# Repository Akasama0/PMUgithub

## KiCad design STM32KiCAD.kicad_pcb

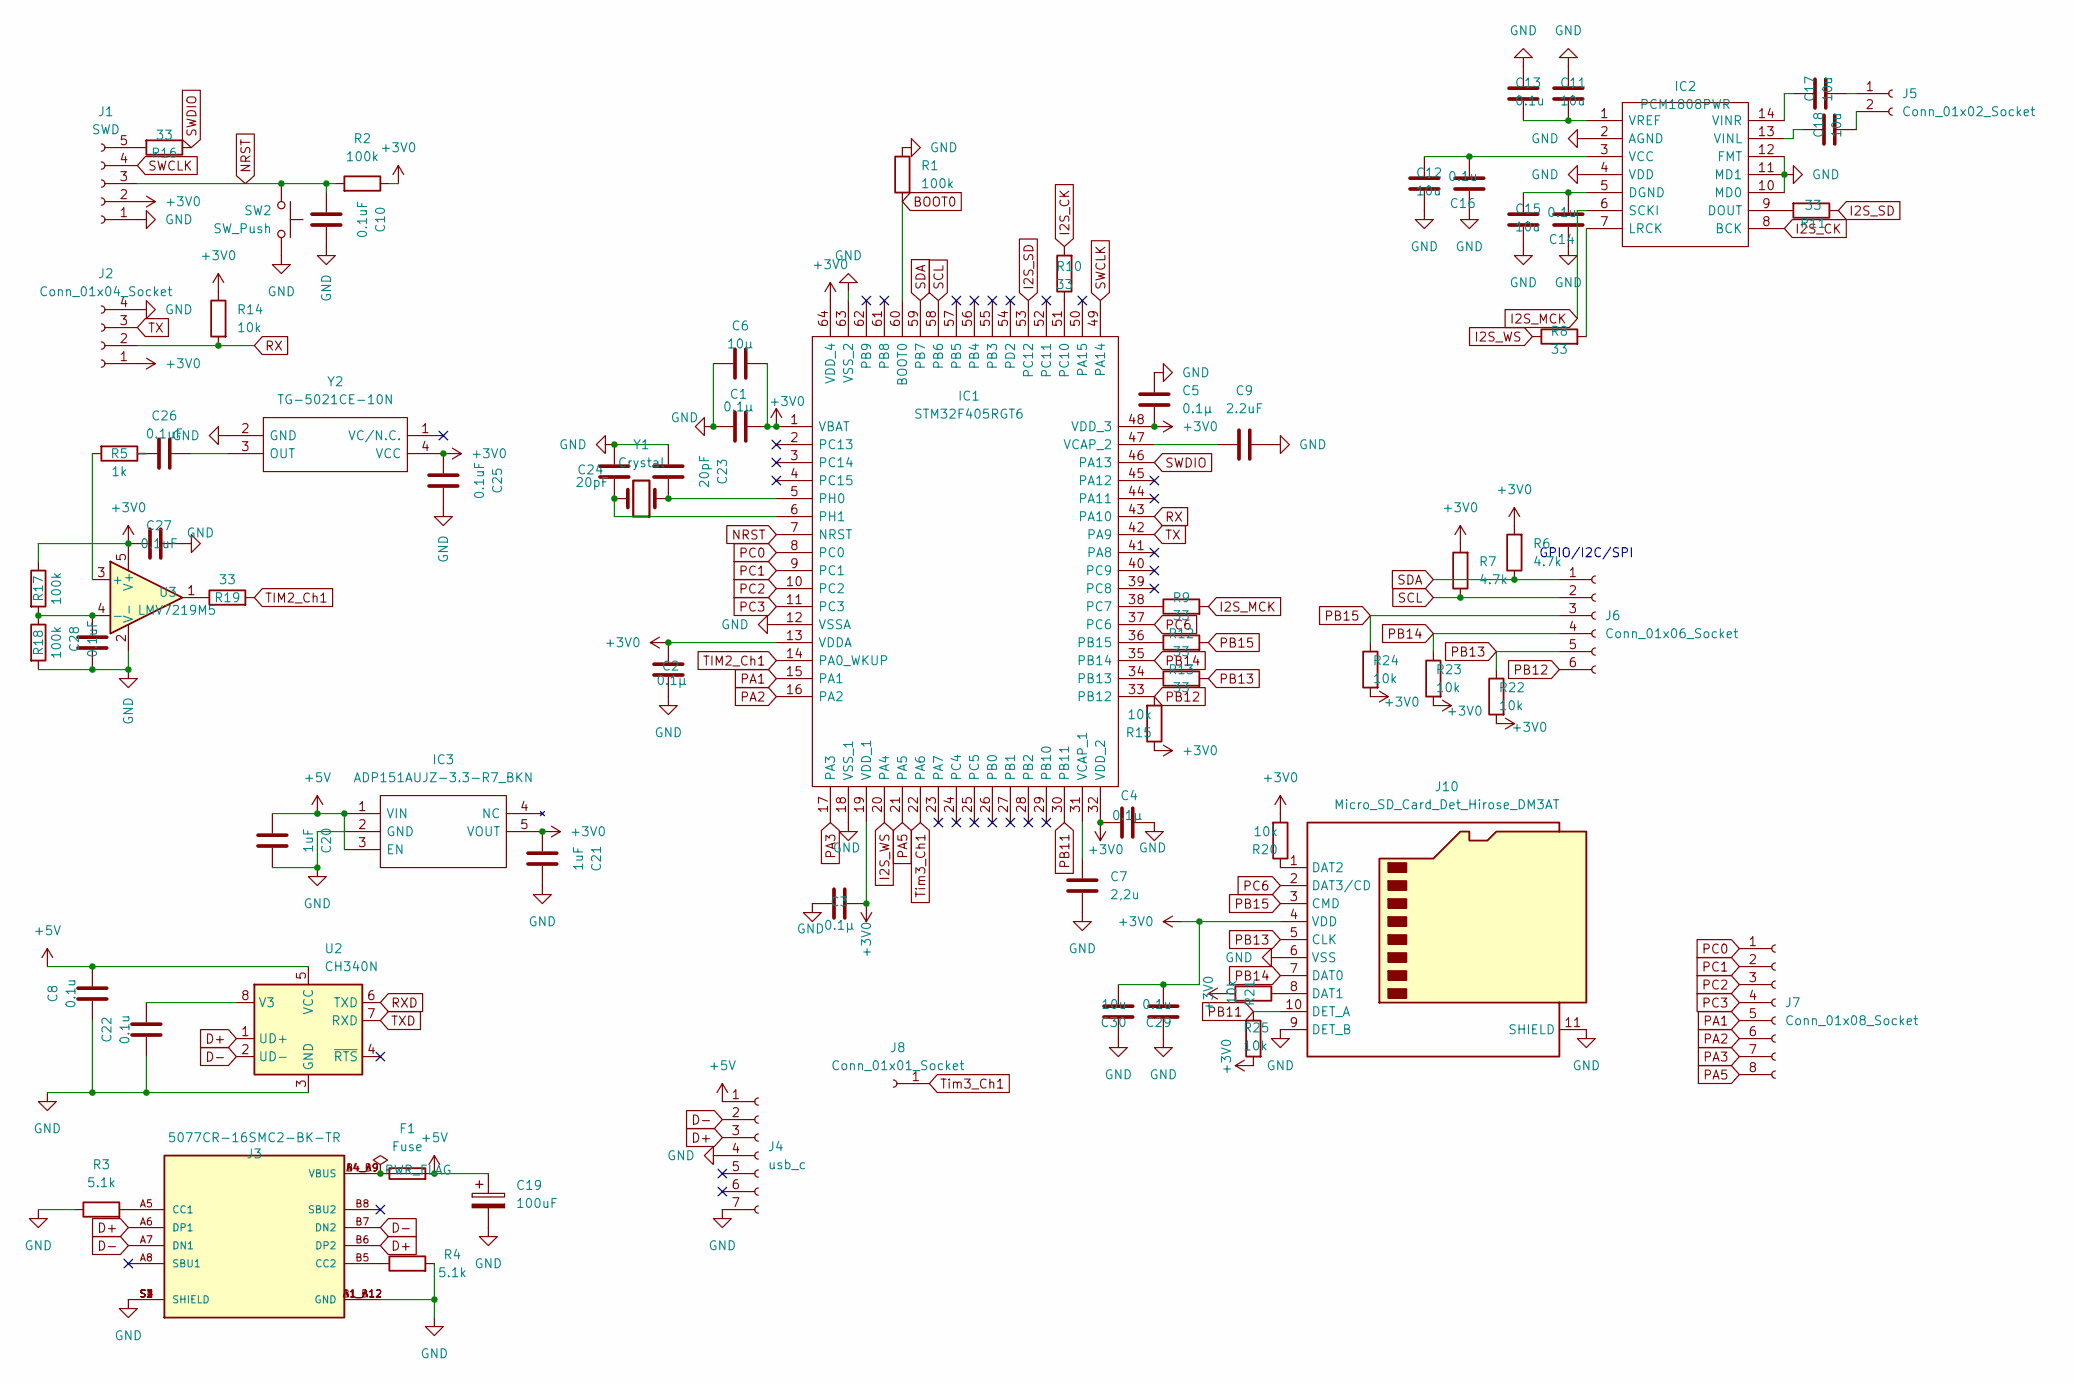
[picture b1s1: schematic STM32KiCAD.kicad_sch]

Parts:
C1, C2, C3, C4, C5: 0.1μ; C_0603_1608Metric_Pad1.08x0.95mm_HandSolder
C6: 10μ; C_0603_1608Metric_Pad1.08x0.95mm_HandSolder
C7: 2,2u; C_0603_1608Metric_Pad1.08x0.95mm_HandSolder
C8, C13, C14, C16, C22, C29: 0.1u; C_0603_1608Metric_Pad1.08x0.95mm_HandSolder
C9: 2.2uF; C_0603_1608Metric_Pad1.08x0.95mm_HandSolder
C10, C25, C26, C27, C28: 0.1uF; C_0603_1608Metric_Pad1.08x0.95mm_HandSolder
C11, C12, C15, C17, C18, C30: 10u; C_0603_1608Metric_Pad1.08x0.95mm_HandSolder
C19: 100uF; C_Radial_D5.0mm_H5.0mm_P2.00mm
C20, C21: 1uF; C_0603_1608Metric_Pad1.08x0.95mm_HandSolder
C23, C24: 20pF; C_0603_1608Metric_Pad1.08x0.95mm_HandSolder
F1: Fuse; Fuse_BelFuse_0ZRE0055FF_L14.0mm_W4.1mm
IC1: STM32F405RGT6; QFP50P1200X1200X160-64N; Manufacturer_Part_Number STM32F405RGT6; Mouser Part Number 511-STM32F405RGT6
IC2: PCM1808PWR; Manufacturer_Part_Number PCM1808PWR; Mouser Part Number 595-PCM1808PWR
IC3: ADP151AUJZ-3.3-R7_BKN; SOT95P280X100-5N; Manufacturer_Part_Number ADP151AUJZ-3.3-R7/BKN
J1: SWD; PinSocket_1x05_P2.54mm_Vertical
J2: Conn_01x04_Socket; PinSocket_1x04_P2.54mm_Vertical
J3: 5077CR-16SMC2-BK-TR; NELTRON_5077CR-16SMC2-BK-TR; PARTREV B
J4: usb_c; PinSocket_1x07_P2.54mm_Vertical
J5: Conn_01x02_Socket; PinSocket_1x02_P2.54mm_Vertical
J6: Conn_01x06_Socket; PinSocket_1x06_P2.54mm_Vertical
J7: Conn_01x08_Socket; PinSocket_1x08_P2.54mm_Vertical
J8: Conn_01x01_Socket; PinSocket_1x01_P2.54mm_Vertical
J10: Micro_SD_Card_Det_Hirose_DM3AT; microSD_HC_Hirose_DM3AT-SF-PEJM5
R1, R2, R17, R18: 100k; R_0603_1608Metric_Pad0.98x0.95mm_HandSolder
R3, R4: 5.1k; R_0603_1608Metric_Pad0.98x0.95mm_HandSolder
R5: 1k; R_0603_1608Metric_Pad0.98x0.95mm_HandSolder
R6, R7: 4.7k; R_0603_1608Metric_Pad0.98x0.95mm_HandSolder
R8, R9, R10, R11, R12, R13, R16, R19: 33; R_0603_1608Metric_Pad0.98x0.95mm_HandSolder
R14, R15, R20, R21, R22, R23, R24, R25: 10k; R_0603_1608Metric_Pad0.98x0.95mm_HandSolder
SW2: SW_Push; SW_PUSH_1P1T_6x3.5mm_H4.3_APEM_MJTP1243
U2: CH340N; SOP-8_3.9x4.9mm_P1.27mm
U3: LMV7219M5; SOT-23-5
Y1: Crystal; Resonator-2Pin_W10.0mm_H5.0mm
Y2: TG-5021CE-10N; TG-5021CE; Manufacturer_Part_Number TG-5021CE-10N

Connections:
+3V0: C1.2, C2.1, C3.2, C4.1, C5.2, C6.2, C21.1, C25.1, C27.1, C29.2, C30.2, IC1.1 (VBAT), IC1.13 (VDDA), IC1.19 (VDD_1), IC1.32 (VDD_2), IC1.48 (VDD_3), IC1.64 (VDD_4), IC3.5 (VOUT), J1.2, J2.1, J10.4 (VDD), R2.1, R6.2, R7.2, R14.1, R15.1, R17.1, R20.2, R21.2, R22.2, R23.2, R24.2, R25.2, U3.5 (V+), Y2.4 (VCC)
+5V: C8.1, C19.1, C20.1, F1.2, IC3.1 (VIN), IC3.3 (EN), J4.1, U2.5 (VCC)
BOOT0: IC1.60 (BOOT0), R1.2
D+: J3.A6 (DP1), J3.B6 (DP2), J4.3, U2.1 (UD+)
D-: J3.A7 (DN1), J3.B7 (DN2), J4.2, U2.2 (UD-)
GND: C1.1, C2.2, C3.1, C4.2, C5.1, C6.1, C7.2, C8.2, C9.2, C10.2, C11.1, C12.2, C13.1, C14.1, C15.2, C16.1, C19.2, C20.2, C21.2, C22.2, C23.1, C24.2, C25.2, C27.2, C28.1, C29.1, C30.1, IC1.12 (VSSA), IC1.18 (VSS_1), IC1.63 (VSS_2), IC2.2 (AGND), IC2.4 (VDD), IC2.10 (MD0), IC2.11 (MD1), IC2.12 (FMT), IC3.2 (GND), J1.1, J2.4, J3.A1_B12 (GND), J3.B1_A12 (GND), J3.S1 (SHIELD), J3.S2 (SHIELD), J3.S3 (SHIELD), J3.S4 (SHIELD), J4.4, J4.7, J10.6 (VSS), J10.9 (DET_B), J10.11 (SHIELD), R1.1, R3.1, R4.2, R18.2, SW2.1, U2.3 (GND), U3.2 (V-), Y2.2 (GND)
I2S_CK: IC2.8 (BCK), R10.2
I2S_MCK: IC2.6 (SCKI), R9.2
I2S_SD: IC1.53 (PC12), R11.1
I2S_WS: IC1.20 (PA4), R8.1
NRST: C10.1, IC1.7 (NRST), J1.3, R2.2, SW2.2
unnamed: C26.1, R5.1
unnamed: F1.1, J3.A4_B9 (VBUS), J3.B4_A9 (VBUS)
unnamed: IC1.34 (PB13), R13.1
unnamed: IC1.36 (PB15), R12.1
unnamed: IC1.38 (PC7), R9.1
unnamed: IC1.51 (PC10), R10.1
unnamed: C23.2, IC1.5 (PH0), Y1.1
unnamed: C24.1, IC1.6 (PH1), Y1.2
unnamed: C7.1, IC1.31 (VCAP_1)
unnamed: C9.1, IC1.47 (VCAP_2)
unnamed: C14.2, C15.1, IC2.5 (DGND)
unnamed: IC2.9 (DOUT), R11.2
unnamed: IC2.7 (LRCK), R8.2
unnamed: C12.1, C16.2, IC2.3 (VCC)
unnamed: C18.1, IC2.13 (VINL)
unnamed: C17.1, IC2.14 (VINR)
unnamed: C11.2, C13.2, IC2.1 (VREF)
unnamed: J1.5, R16.2
unnamed: J3.A5 (CC1), R3.2
unnamed: J3.B5 (CC2), R4.1
unnamed: C17.2, J5.1
unnamed: C18.2, J5.2
unnamed: J10.8 (DAT1), R21.1
unnamed: J10.1 (DAT2), R20.1
unnamed: R19.1, U3.1
unnamed: C22.1, U2.8 (V3)
unnamed: R5.2, U3.3 (+)
unnamed: C28.2, R17.2, R18.1, U3.4 (-)
unnamed: C26.2, Y2.3 (OUT)
PA1: IC1.15 (PA1), J7.5
PA2: IC1.16 (PA2), J7.6
PA3: IC1.17 (PA3), J7.7
PA5: IC1.21 (PA5), J7.8
PB11: IC1.30 (PB11), J10.10 (DET_A), R25.1
PB12: IC1.33 (PB12), J6.6, R15.2
PB13: J6.5, J10.5 (CLK), R13.2, R22.1
PB14: IC1.35 (PB14), J6.4, J10.7 (DAT0), R23.1
PB15: J6.3, J10.3 (CMD), R12.2, R24.1
PC0: IC1.8 (PC0), J7.1
PC1: IC1.9 (PC1), J7.2
PC2: IC1.10 (PC2), J7.3
PC3: IC1.11 (PC3), J7.4
PC6: IC1.37 (PC6), J10.2 (DAT3/CD)
RX: IC1.43 (PA10), J2.2, R14.2
RXD: U2.6 (TXD)
SCL: IC1.58 (PB6), J6.2, R7.1
SDA: IC1.59 (PB7), J6.1, R6.1
SWCLK: IC1.49 (PA14), J1.4
SWDIO: IC1.46 (PA13), R16.1
TIM2_Ch1: IC1.14 (PA0_WKUP), R19.2
TX: IC1.42 (PA9), J2.3
TXD: U2.7 (RXD)
Tim3_Ch1: IC1.22 (PA6), J8.1

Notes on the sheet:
GPIO/I2C/SPI

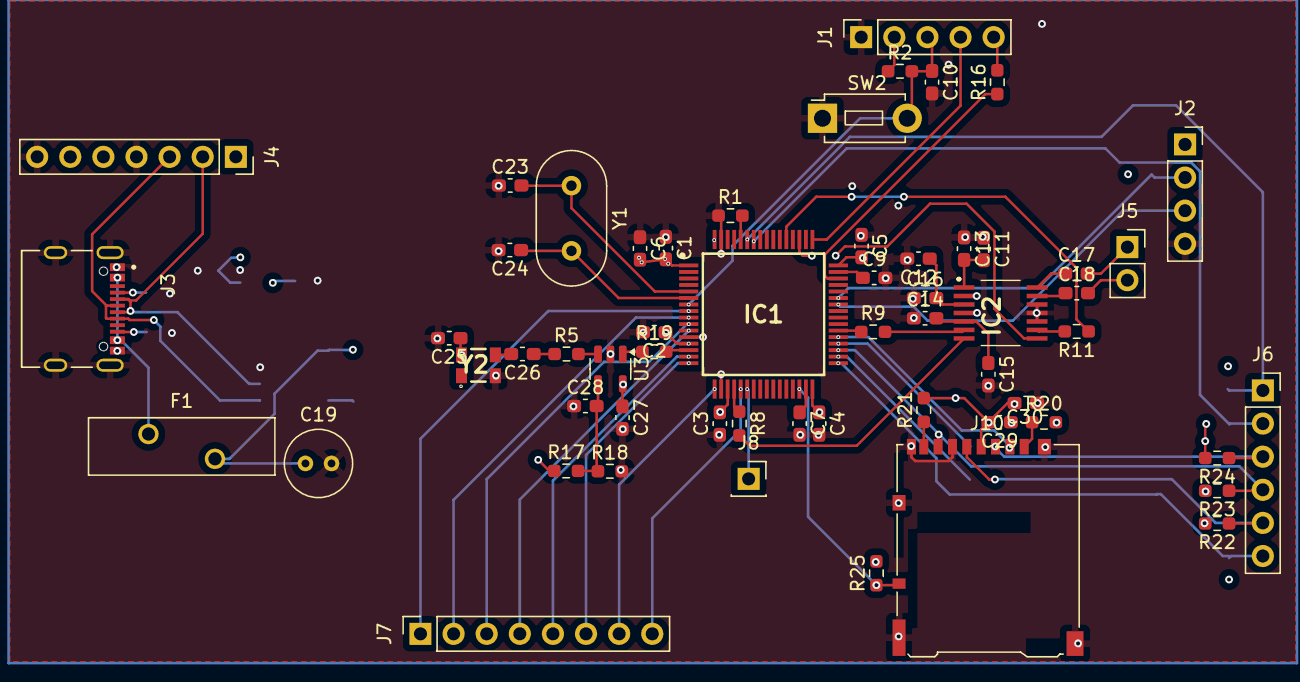
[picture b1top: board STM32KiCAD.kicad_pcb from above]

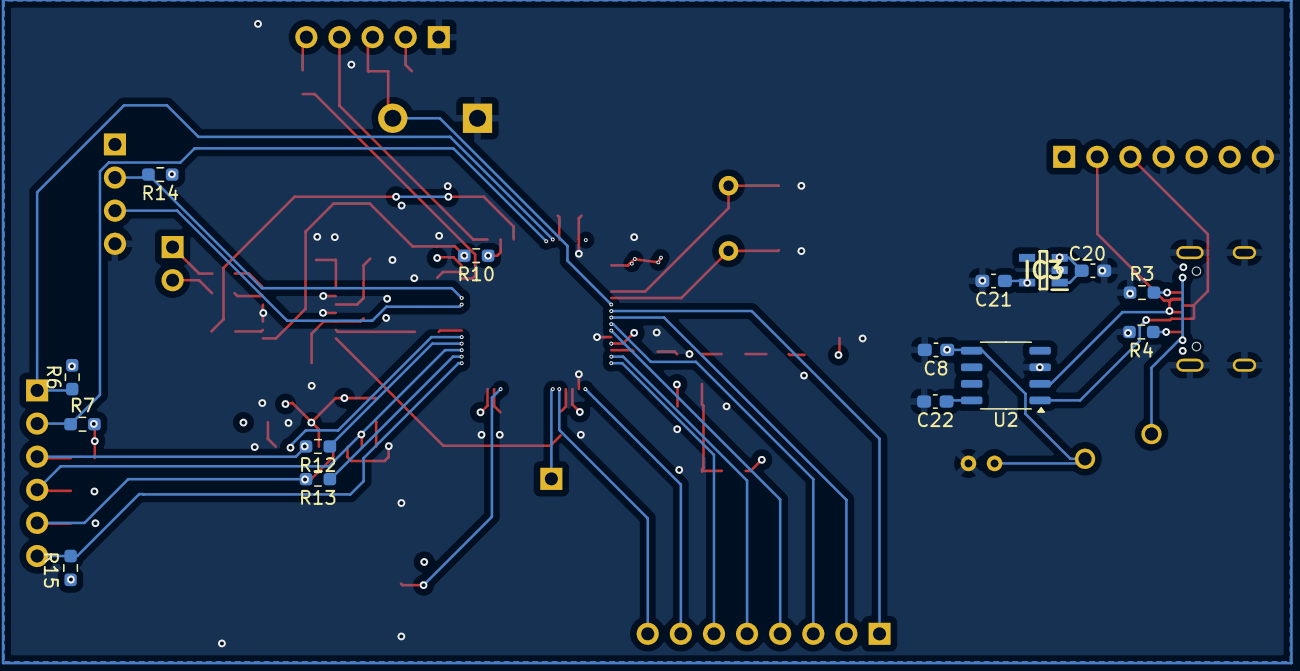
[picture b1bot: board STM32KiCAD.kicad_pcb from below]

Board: 4 copper layers, 73 parts (15 on the bottom side), 62 nets.

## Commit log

2026-04-03 first-ver
